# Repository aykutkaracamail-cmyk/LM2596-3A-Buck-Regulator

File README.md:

# KiCAD LM2596 Buck Regulator Project

Bu projede giriş gerilimini düşürerek çıkışa aktarmak amaçlanmıştır. Giriş gerilimini düşüren bu tip devrelere SMPS (Switched-Mode Power Supply) devreleri denilmiş olup, bu proje özelinde LM2596-ADJ entegresi kullanılmıştır. 

Çıkıştaki ani akım ihtiyacını karşılayabilmek ve voltaj çakılmasını engelleyebilmek için giriş kısmında 50V dayanımlı iki tane 470 uF'lık polarize kondansatör kullanılmıştır. Anahtarın açık olduğu esnada yük üzerindeki akımı kaybetmemek amacıyla endüktans 68 uH olarak seçilmiş olup, devreden geçecek olan maksimum akımın 3A düzeyinde olması planlandığından ters yön diyotu Schottky (5A) olarak seçilmiştir. Ayrıca yükün üstündeki gerilimin ripple (dalgalanma) katsayısının düşürülmesi amacıyla çıkışa paralel bağlı olan iki tane 220 uF'lık 35V dayanımlı polarize kondansatör kullanılmıştır. Versiyonlar arası komponentler değişiklik gösterebilir. Güncel stok durumları ve üretim maaliyetleri nedeniyle komponentler değiştirilmiştir.

📊 LTspice Simülasyon Sonucu

📊 PCB İlk Bakış

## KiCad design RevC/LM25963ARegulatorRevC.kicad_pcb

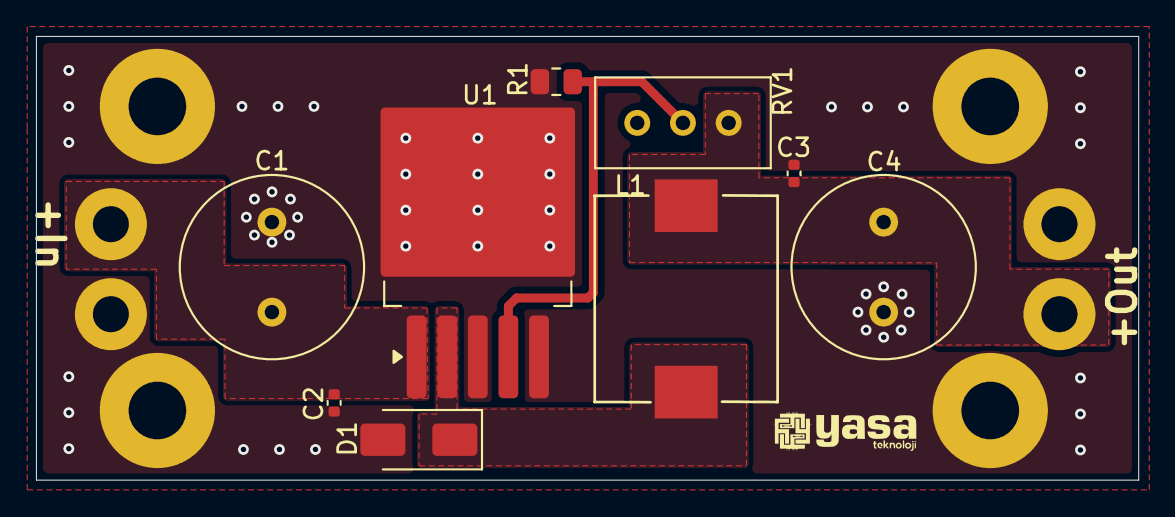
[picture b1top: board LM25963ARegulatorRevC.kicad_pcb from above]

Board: 2 copper layers, 61.2 x 24.6 mm, 9 parts (0 on the bottom side), 5 nets.

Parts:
C1, C4: 470 uF 50 V; C_Radial_D10.0mm_H20.0mm_P5.00mm
C2, C3: 100 nF 50 V; C_0402_1005Metric
D1: 3A 60 V; D_SMA
L1: 47 uH 3A ISAT 4.5 A; IND-SMD_L11.5-W10.0_SMMS1040
R1: 1K Ohm 150 V 125 mW; R_0805_2012Metric
RV1: 10 K Ohm Multiturn; Potentiometer_Bourns_3296W_Vertical
U1: LM2596S-ADJ; TO-263-5_TabPin3

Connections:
GND: C1.2, C2.2, C3.2, C4.2, D1.2 (A), R1.1, U1.3 (GND), U1.5 (~ON/OFF)
unnamed: D1.1 (K), L1.1, U1.2 (OUT)
unnamed: C1.1, C2.1, U1.1 (VIN)
unnamed: C3.1, C4.1, L1.2, RV1.3
unnamed: R1.2, RV1.2, U1.4 (FB)

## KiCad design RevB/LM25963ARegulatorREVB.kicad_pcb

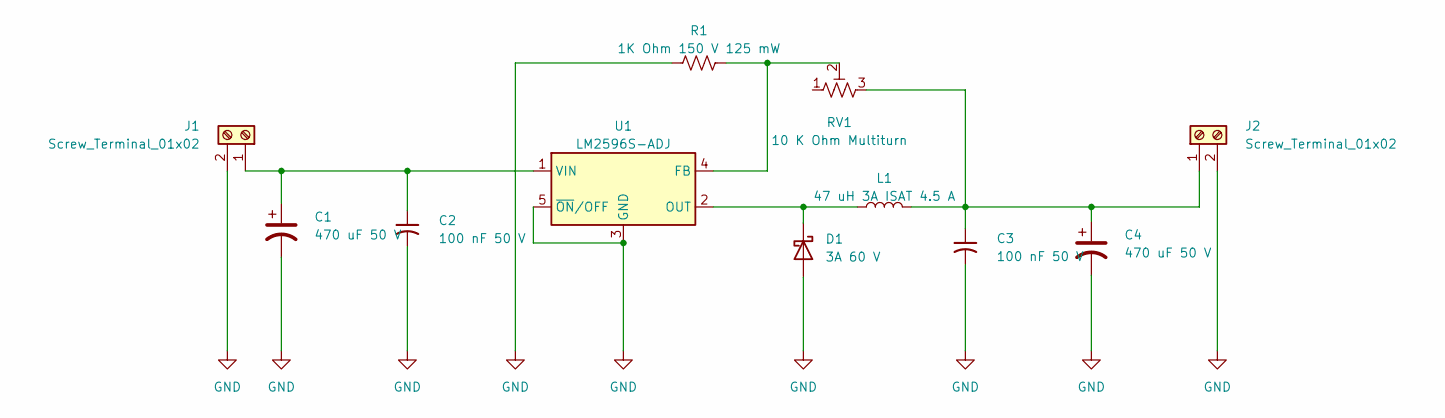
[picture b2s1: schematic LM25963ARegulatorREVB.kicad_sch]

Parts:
C1, C4: 470 uF 50 V; C_Radial_D10.0mm_H20.0mm_P5.00mm
C2, C3: 100 nF 50 V; C_0402_1005Metric
D1: 3A 60 V; D_SMA
J1, J2: Screw_Terminal_01x02; CONN-TH_DB301V-3.5-2P-GN
L1: 47 uH 3A ISAT 4.5 A; IND-SMD_L11.5-W10.0_SMMS1040
R1: 1K Ohm 150 V 125 mW; R_0805_2012Metric
RV1: 10 K Ohm Multiturn; Potentiometer_Bourns_3296W_Vertical
U1: LM2596S-ADJ; TO-263-5_TabPin3

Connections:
GND: C1.2, C2.2, C3.2, C4.2, D1.2 (A), J1.2, J2.2, R1.1, U1.3 (GND), U1.5 (~ON/OFF)
unnamed: D1.1 (K), L1.1, U1.2 (OUT)
unnamed: C1.1, C2.1, J1.1, U1.1 (VIN)
unnamed: C3.1, C4.1, J2.1, L1.2, RV1.3
unnamed: R1.2, RV1.2, U1.4 (FB)

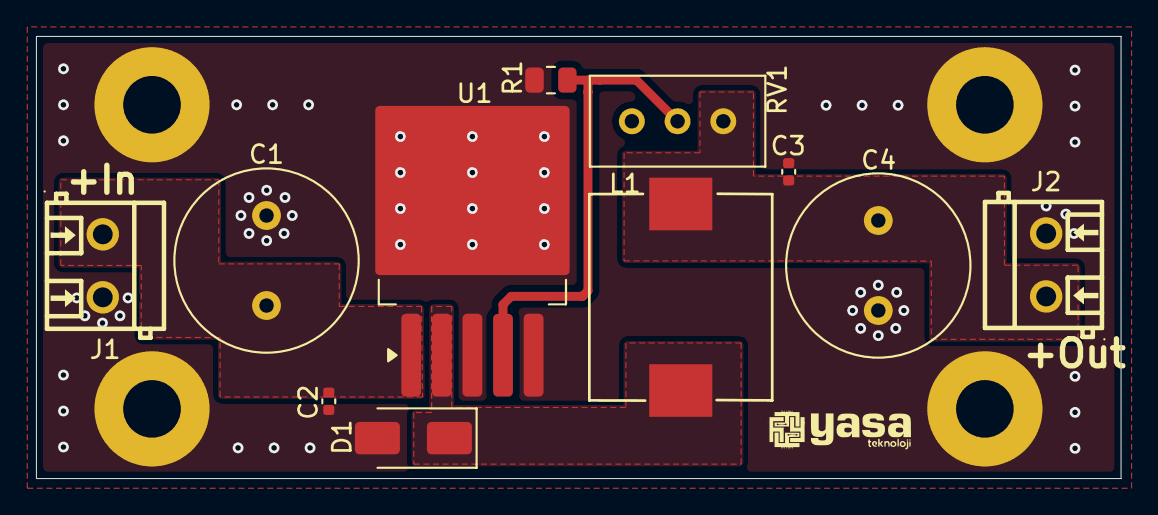
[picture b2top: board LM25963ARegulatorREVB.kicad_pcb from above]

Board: 2 copper layers, 60.3 x 24.6 mm, 11 parts (0 on the bottom side), 5 nets.
